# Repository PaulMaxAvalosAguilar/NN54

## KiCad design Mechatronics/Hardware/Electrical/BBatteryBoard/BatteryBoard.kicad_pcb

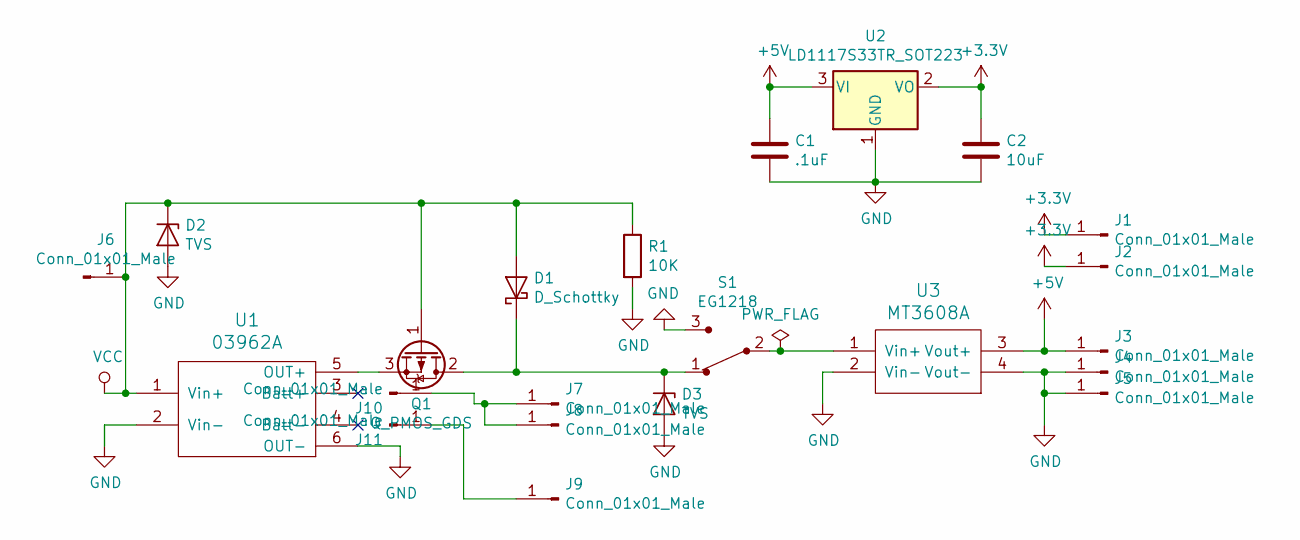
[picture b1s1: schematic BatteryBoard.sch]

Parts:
C1: .1uF; C_Disc_D9.0mm_W5.0mm_P5.00mm
C2: 10uF; C_Disc_D9.0mm_W5.0mm_P5.00mm
D1: D_Schottky; D_DO-201AD_P15.24mm_Horizontal
D2, D3: TVS; D_DO-201AD_P15.24mm_Horizontal
J1, J2, J3, J4, J5, J6, J7, J8, J9, J10, J11: Conn_01x01_Male; PinHeader_1x01_P2.54mm_Vertical
Q1: Q_PMOS_GDS; TO-220-3_Horizontal_TabDown
R1: 10K; R_Axial_DIN0414_L11.9mm_D4.5mm_P15.24mm_Horizontal
S1: EG1218; Switch_Slide_11.6x4mm_EG1218; MPN EG1218; Digi-Key_PN EG1903-ND
U1: 03962A
U2: LD1117S33TR_SOT223; TO-220-3_Horizontal_TabDown
U3: MT3608A; Mt3608

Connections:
+3V3: C2.1, J1.1, J2.1, U2.2 (VO)
+5V: C1.1, J3.1, U2.3 (VI), U3.3 (Vout+)
GND: C1.2, C2.2, D2.2 (A), D3.2 (A), J4.1, J5.1, R1.2, S1.3, U1.2 (Vin-), U1.6 (OUT-), U2.1 (GND), U3.2 (Vin-), U3.4 (Vout-)
unnamed: D1.1 (K), D3.1 (K), Q1.2 (D), S1.1
unnamed: J7.1, J8.1, J10.1
unnamed: J9.1, J11.1
unnamed: Q1.3 (S), U1.5 (OUT+)
unnamed: S1.2, U3.1 (Vin+)
VCC: D1.2 (A), D2.1 (K), J6.1, Q1.1 (G), R1.1, U1.1 (Vin+)

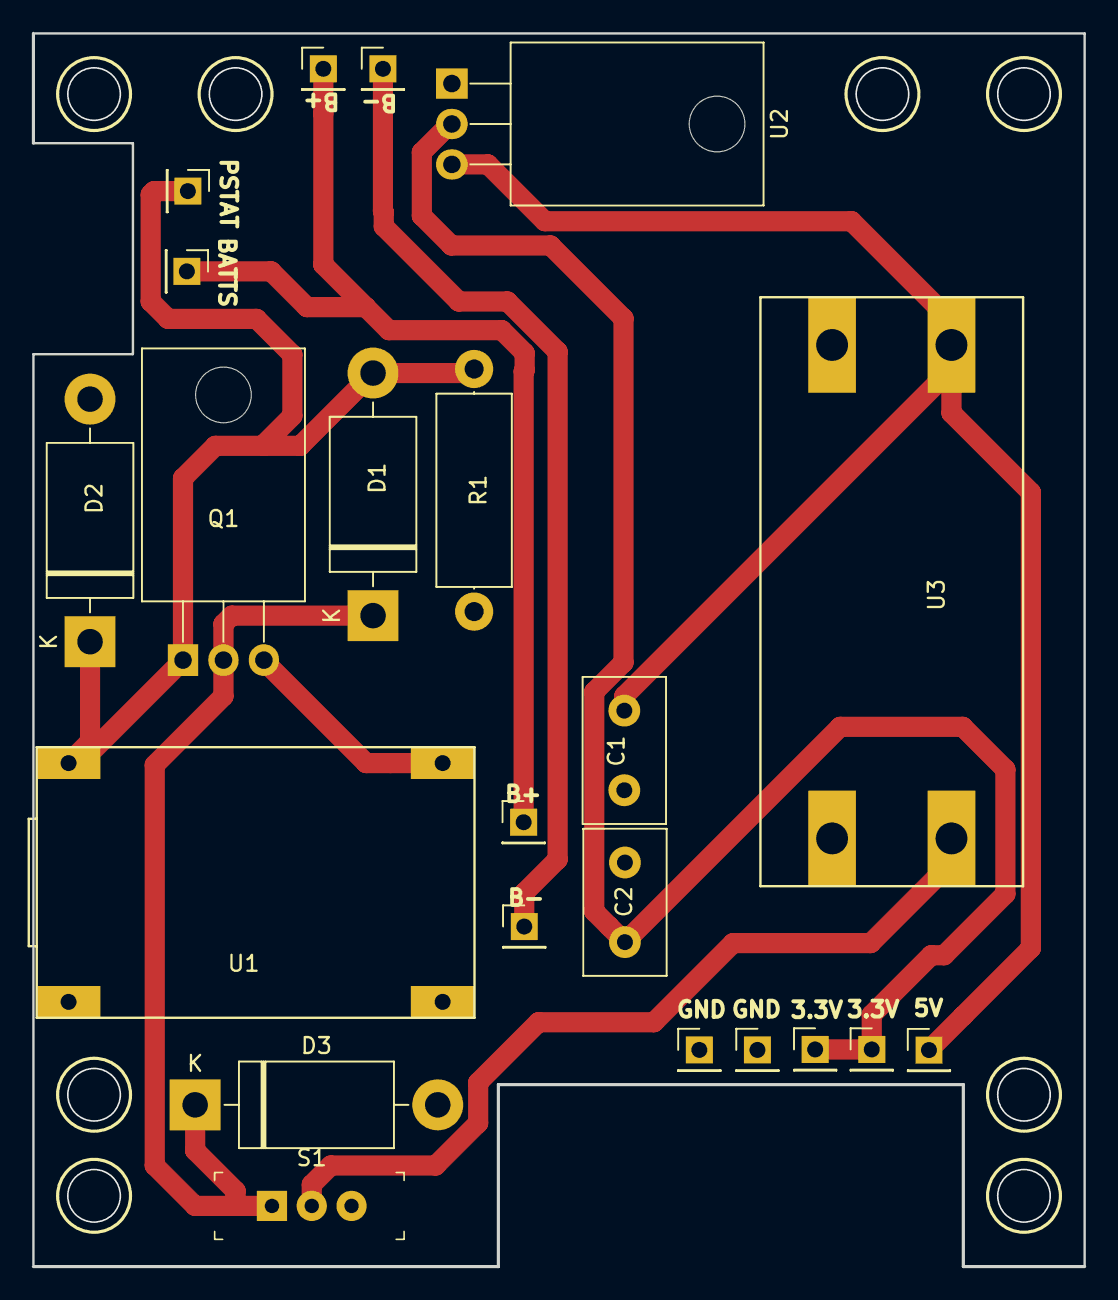
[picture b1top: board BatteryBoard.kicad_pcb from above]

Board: 2 copper layers, 66.0 x 77.5 mm, 22 parts (0 on the bottom side), 9 nets.

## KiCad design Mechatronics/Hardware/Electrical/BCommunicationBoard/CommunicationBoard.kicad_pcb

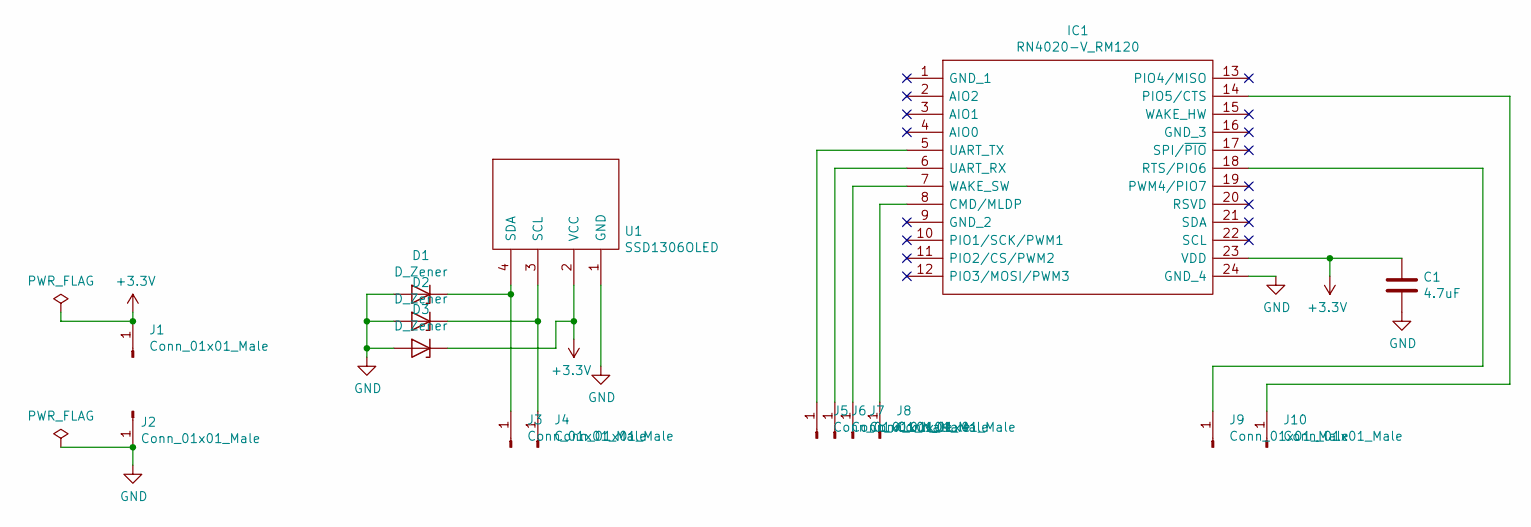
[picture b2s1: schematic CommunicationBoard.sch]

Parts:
C1: 4.7uF; C_Disc_D9.0mm_W5.0mm_P5.00mm
D1, D2, D3: D_Zener; D_DO-201AD_P15.24mm_Horizontal
IC1: RN4020-V_RM120; Bluetooth_Module_RN4020; Manufacturer_Part_Number RN4020-V/RM120
J1, J2, J3, J4, J5, J6, J7, J8, J9, J10: Conn_01x01_Male; PinHeader_1x01_P2.54mm_Vertical
U1: SSD1306OLED; SSD1306

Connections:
+3V3: C1.1, D3.1 (K), IC1.23 (VDD), J1.1, U1.2 (VCC)
GND: C1.2, D1.2 (A), D2.2 (A), D3.2 (A), IC1.24 (GND_4), J2.1, U1.1 (GND)
unnamed: D1.1 (K), J3.1, U1.4 (SDA)
unnamed: D2.1 (K), J4.1, U1.3 (SCL)
unnamed: IC1.5 (UART_TX), J5.1
unnamed: IC1.6 (UART_RX), J6.1
unnamed: IC1.7 (WAKE_SW), J7.1
unnamed: IC1.8 (CMD/MLDP), J8.1
unnamed: IC1.14 (PIO5/CTS), J10.1
unnamed: IC1.18 (RTS/PIO6), J9.1

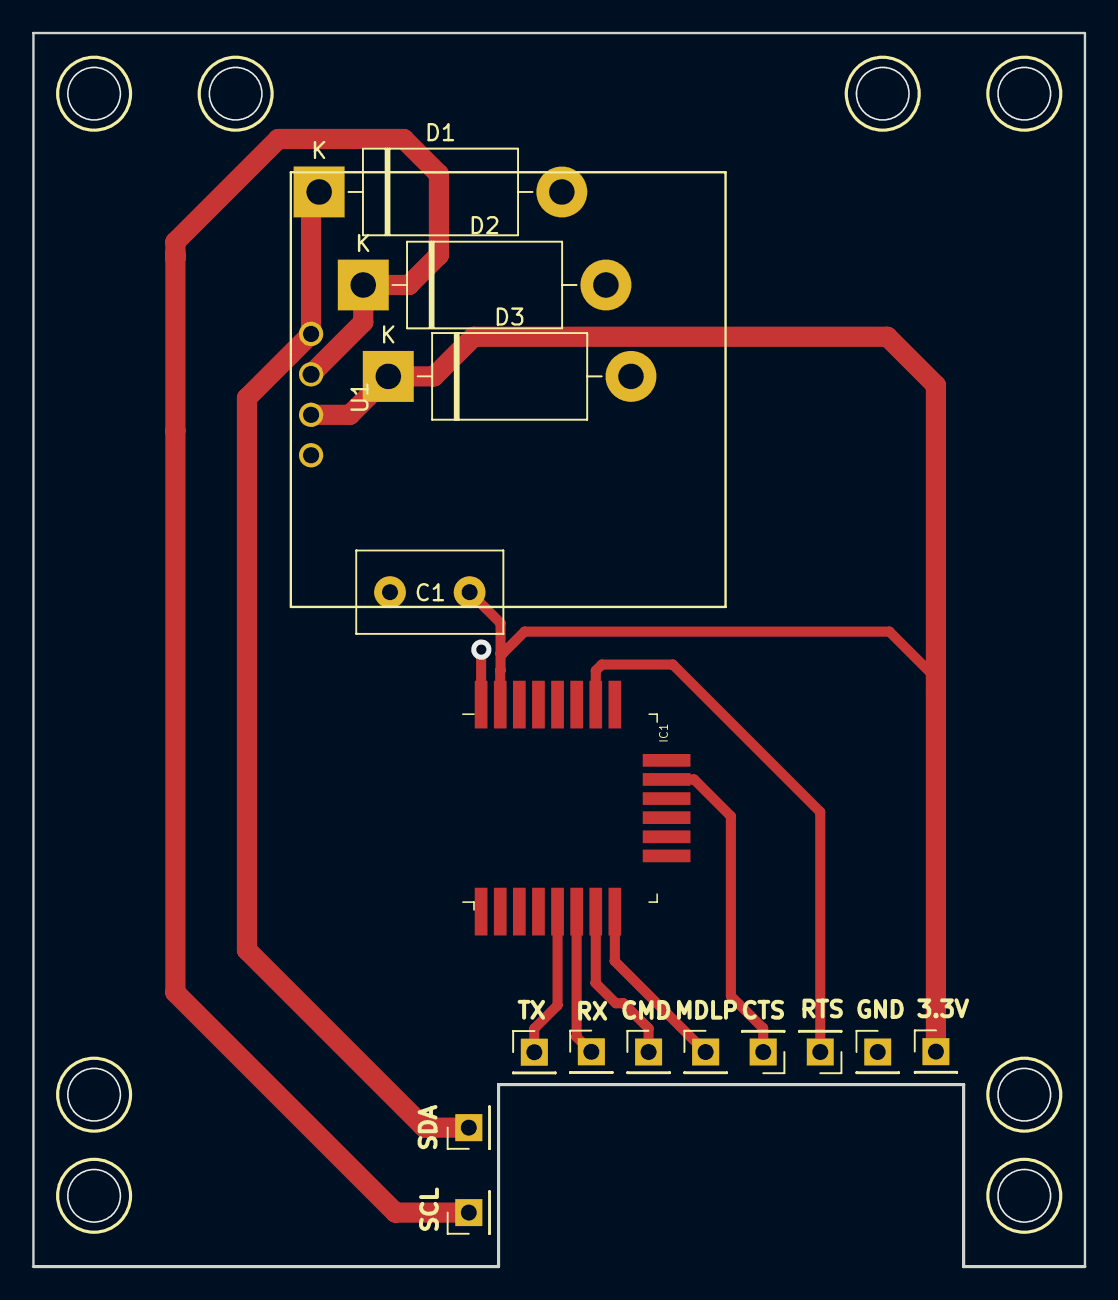
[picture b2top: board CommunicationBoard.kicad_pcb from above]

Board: 2 copper layers, 66.0 x 77.5 mm, 16 parts (0 on the bottom side), 10 nets.

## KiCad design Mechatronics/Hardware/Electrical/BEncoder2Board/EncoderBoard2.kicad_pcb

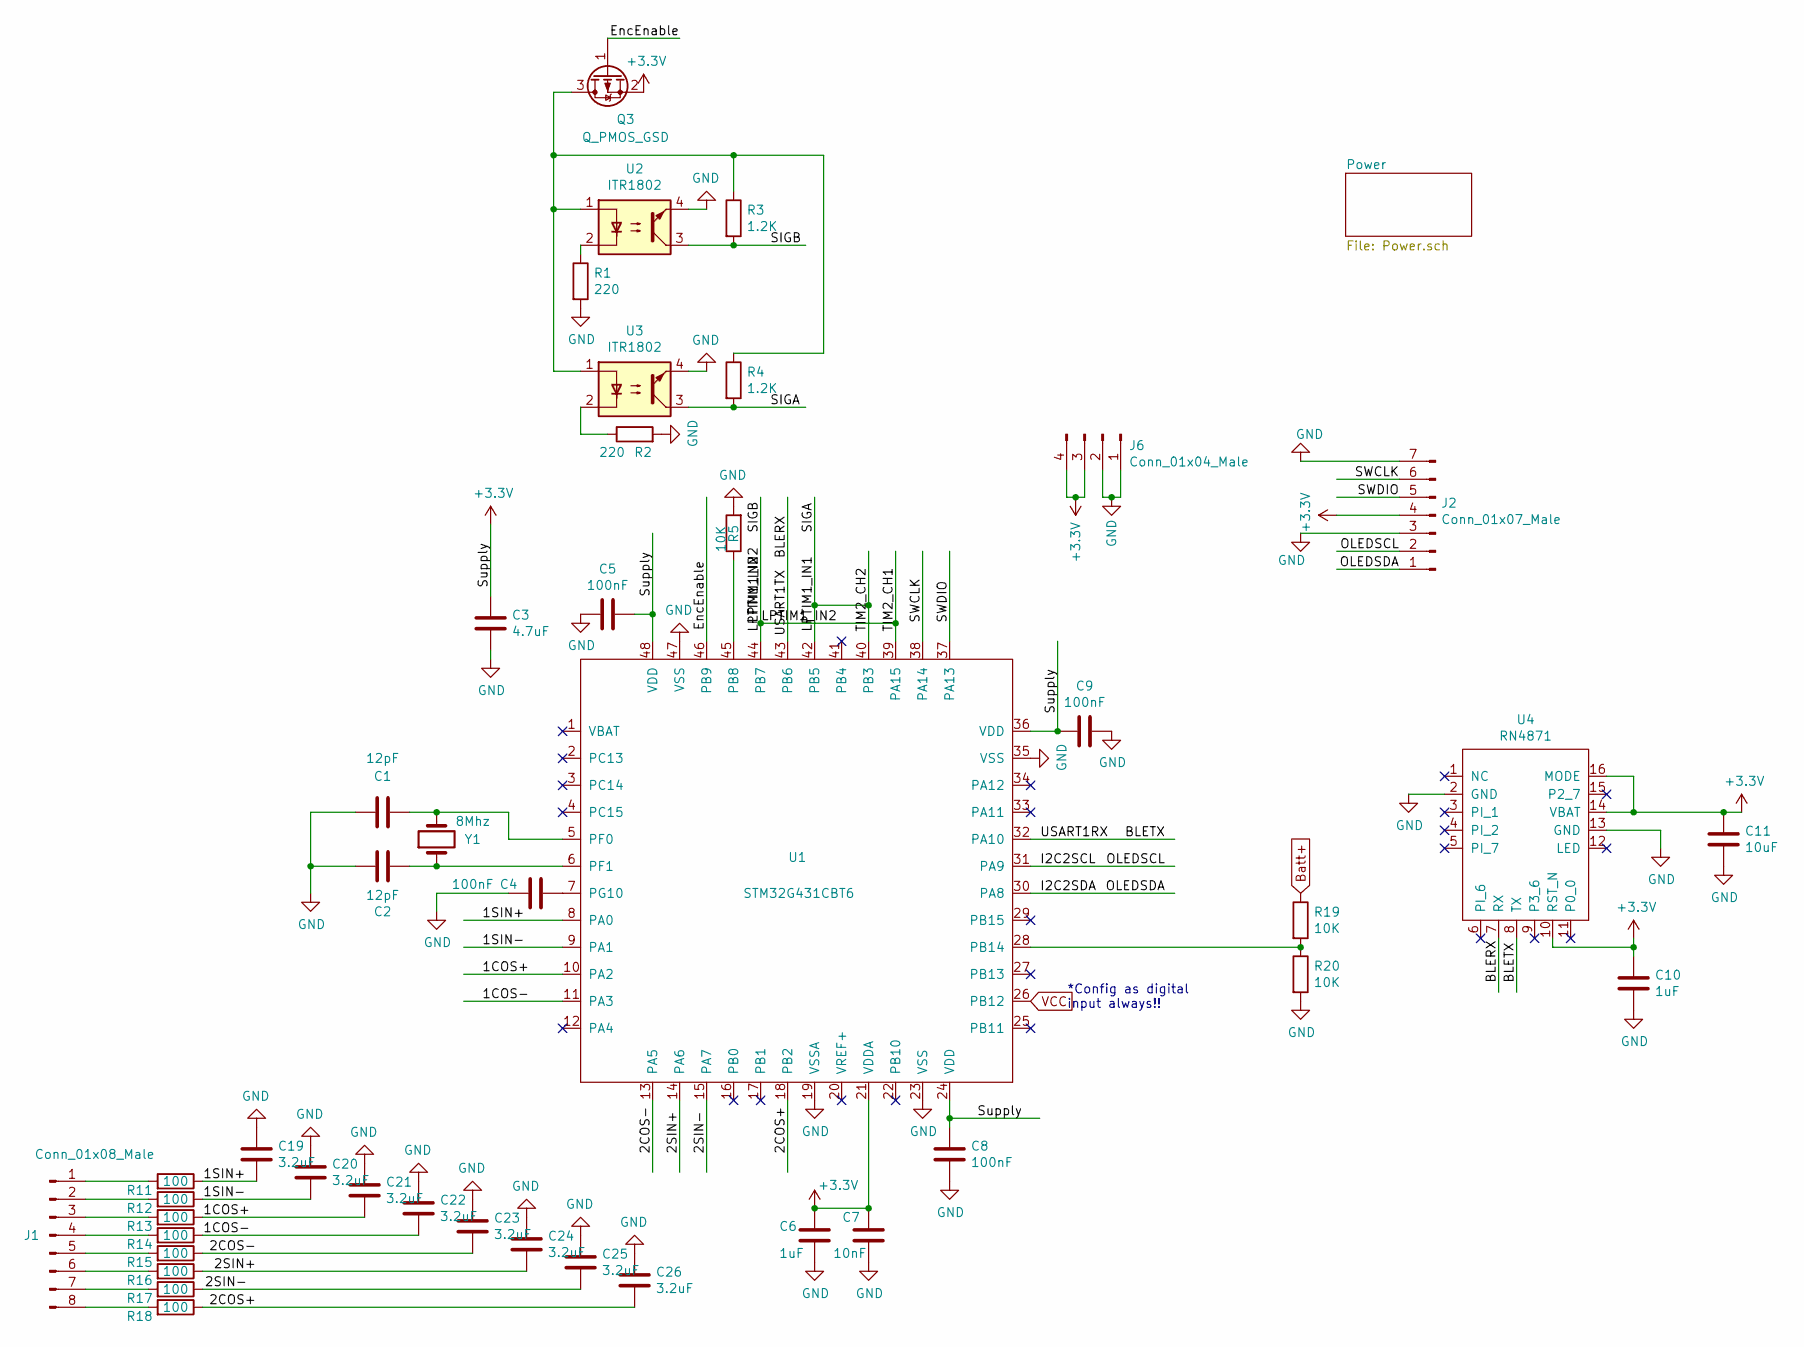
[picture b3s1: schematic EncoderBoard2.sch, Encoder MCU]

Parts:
C1, C2: 12pF; C_0603_1608Metric_Pad1.05x0.95mm_HandSolder
C3: 4.7uF; C_0603_1608Metric_Pad1.05x0.95mm_HandSolder
C4, C5, C8, C9: 100nF; C_0603_1608Metric_Pad1.05x0.95mm_HandSolder
C6, C10: 1uF; C_0603_1608Metric_Pad1.05x0.95mm_HandSolder
C7: 10nF; C_0603_1608Metric_Pad1.05x0.95mm_HandSolder
C11: 10uF; C_0603_1608Metric_Pad1.05x0.95mm_HandSolder
C19, C20, C21, C22, C23, C24, C25, C26: 3.2uF; C_0603_1608Metric_Pad1.05x0.95mm_HandSolder
J1: Conn_01x08_Male; PinHeader_1x08_P2.54mm_Vertical
J2: Conn_01x07_Male; PinHeader_1x07_P2.54mm_Vertical
J6: Conn_01x04_Male; PinHeader_2x02_P2.54mm_Vertical
Q3: Q_PMOS_GSD; SOT-23
R1, R2: 220; R_0603_1608Metric_Pad1.05x0.95mm_HandSolder
R3, R4: 1.2K; R_0603_1608Metric_Pad1.05x0.95mm_HandSolder
R5, R19, R20: 10K; R_0603_1608Metric_Pad1.05x0.95mm_HandSolder
R11, R12, R13, R14, R15, R16, R17, R18: 100; R_0603_1608Metric_Pad1.05x0.95mm_HandSolder
U1: STM32G431CBT6; LQFP-48_7x7mm_P0.5mm
U2, U3: ITR1802; OptointerrupterSmall
U4: RN4871; Bluetooth_Module_RN4871
Y1: 8Mhz; Crystal_HC49-U_Vertical

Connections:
+3V3: C3.1, C5.1, C6.1, C7.1, C8.1, C9.2, C10.1, C11.1, J2.4, J6.3, J6.4, Q3.2 (S), U1.21 (VDDA), U1.24 (VDD), U1.36 (VDD), U1.48 (VDD), U4.10 (RST_N), U4.14 (VBAT), U4.16 (MODE); also elsewhere on the board
/1COS+: C21.2, R13.1, U1.10 (PA2)
/1COS-: C22.2, R14.1, U1.11 (PA3)
/1SIN+: C19.2, R11.1, U1.8 (PA0)
/1SIN-: C20.2, R12.1, U1.9 (PA1)
/2COS+: C26.2, R18.1, U1.18 (PB2)
/2COS-: C23.2, R15.1, U1.13 (PA5)
/2SIN+: C24.2, R16.1, U1.14 (PA6)
/2SIN-: C25.2, R17.1, U1.15 (PA7)
/BLERX: U1.43 (PB6), U4.7 (RX)
/BLETX: U1.32 (PA10), U4.8 (TX)
/EncEnable: Q3.1 (G), U1.46 (PB9)
/I2C2SCL: J2.2, U1.31 (PA9)
/I2C2SDA: J2.1, U1.30 (PA8)
/LPTIM1_IN1: R4.2, U1.40 (PB3), U1.42 (PB5), U3.3
/LPTIM1_IN2: R3.2, U1.39 (PA15), U1.44 (PB7), U2.3
/SWCLK: J2.6, U1.38 (PA14)
/SWDIO: J2.5, U1.37 (PA13)
Batt+: R19.1; also elsewhere on the board
GND: C1.1, C2.1, C3.2, C4.2, C5.2, C6.2, C7.2, C8.2, C9.1, C10.2, C11.2, C19.1, C20.1, C21.1, C22.1, C23.1, C24.1, C25.1, C26.1, J2.3, J2.7, J6.1, J6.2, R1.2, R2.2, R5.2, R20.2, U1.19 (VSSA), U1.23 (VSS), U1.35 (VSS), U1.47 (VSS), U2.4, U3.4, U4.2 (GND), U4.13 (GND); also elsewhere on the board
unnamed: C1.2, U1.5 (PF0), Y1.2
unnamed: C2.2, U1.6 (PF1), Y1.1
unnamed: C4.1, U1.7 (PG10)
unnamed: J1.1, R11.2
unnamed: J1.2, R12.2
unnamed: J1.3, R13.2
unnamed: J1.4, R14.2
unnamed: J1.5, R15.2
unnamed: J1.6, R16.2
unnamed: J1.7, R17.2
unnamed: J1.8, R18.2
unnamed: Q3.3 (D), R3.1, R4.1, U2.1, U3.1
unnamed: R1.1, U2.2
unnamed: R2.1, U3.2
unnamed: R5.1, U1.45 (PB8)
unnamed: R19.2, R20.1, U1.28 (PB14)
VCC: U1.26 (PB12); also elsewhere on the board

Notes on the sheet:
*Config as digital input always!!

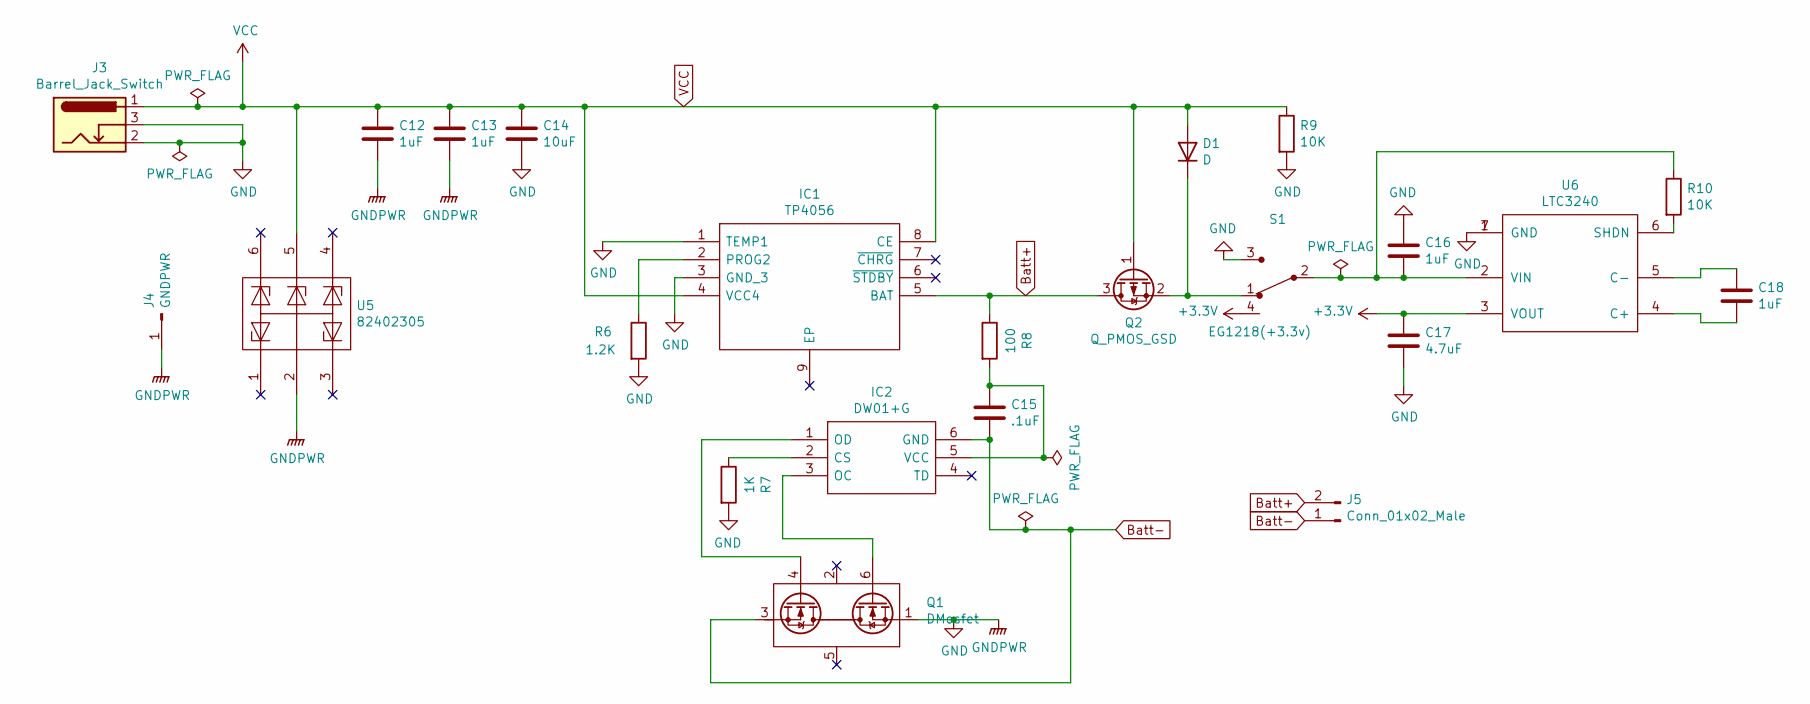
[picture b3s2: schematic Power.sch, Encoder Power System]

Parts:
C12, C13, C16, C18: 1uF; C_0603_1608Metric_Pad1.05x0.95mm_HandSolder
C14: 10uF; C_0603_1608Metric_Pad1.05x0.95mm_HandSolder
C15: .1uF; C_0603_1608Metric_Pad1.05x0.95mm_HandSolder
C17: 4.7uF; C_0603_1608Metric_Pad1.05x0.95mm_HandSolder
D1: D; D_SMA
IC1: TP4056; Sop(8); Manufacturer_Part_Number TP4056
IC2: DW01+G; Sot-23(6); Manufacturer_Part_Number DW01+G
J3: Barrel_Jack_Switch; BarrelJack_Horizontal
J4: GNDPWR; PinHeader_1x01_P2.54mm_Vertical
J5: Conn_01x02_Male; PinHeader_1x02_P2.54mm_Vertical
Q1: DMosfet; Sot-23(6)
Q2: Q_PMOS_GSD; SOT-23
R6: 1.2K; R_0603_1608Metric_Pad1.05x0.95mm_HandSolder
R7: 1K; R_0603_1608Metric_Pad1.05x0.95mm_HandSolder
R8: 100; R_0603_1608Metric_Pad1.05x0.95mm_HandSolder
R9, R10: 10K; R_0603_1608Metric_Pad1.05x0.95mm_HandSolder
S1: EG1218(+3.3v); PinHeader_1x04_P2.54mm_Vertical; MPN EG1218; Digi-Key_PN EG1903-ND
U5: 82402305; Sot-23(6)
U6: LTC3240; DFN-6_DC

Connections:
+3V3: C17.1, S1.4, U6.3 (VOUT); also elsewhere on the board
Batt+: IC1.5 (BAT), J5.2, Q2.3 (D), R8.1; also elsewhere on the board
Batt-: C15.2, IC2.6 (GND), J5.1, Q1.3 (S)
GND: C12.2, C13.2, C14.2, C16.1, C17.2, IC1.1 (TEMP1), IC1.3 (GND_3), J3.2, J3.3, J4.1, Q1.1 (S), R6.2, R7.2, R9.2, S1.3, U5.2, U6.1 (GND), U6.7 (GND); also elsewhere on the board
unnamed: C15.1, IC2.5 (VCC), R8.2
unnamed: C16.2, R10.1, S1.2, U6.2 (VIN)
unnamed: C18.1, U6.5 (C-)
unnamed: C18.2, U6.4 (C+)
unnamed: D1.1 (K), Q2.2 (S), S1.1
unnamed: IC1.2 (PROG2), R6.1
unnamed: IC2.1 (OD), Q1.4 (G)
unnamed: IC2.2 (CS), R7.1
unnamed: IC2.3 (OC), Q1.6 (G)
unnamed: R10.2, U6.6 (SHDN)
VCC: C12.1, C13.1, C14.1, D1.2 (A), IC1.4 (VCC4), IC1.8 (CE), J3.1, Q2.1 (G), R9.1, U5.5; also elsewhere on the board

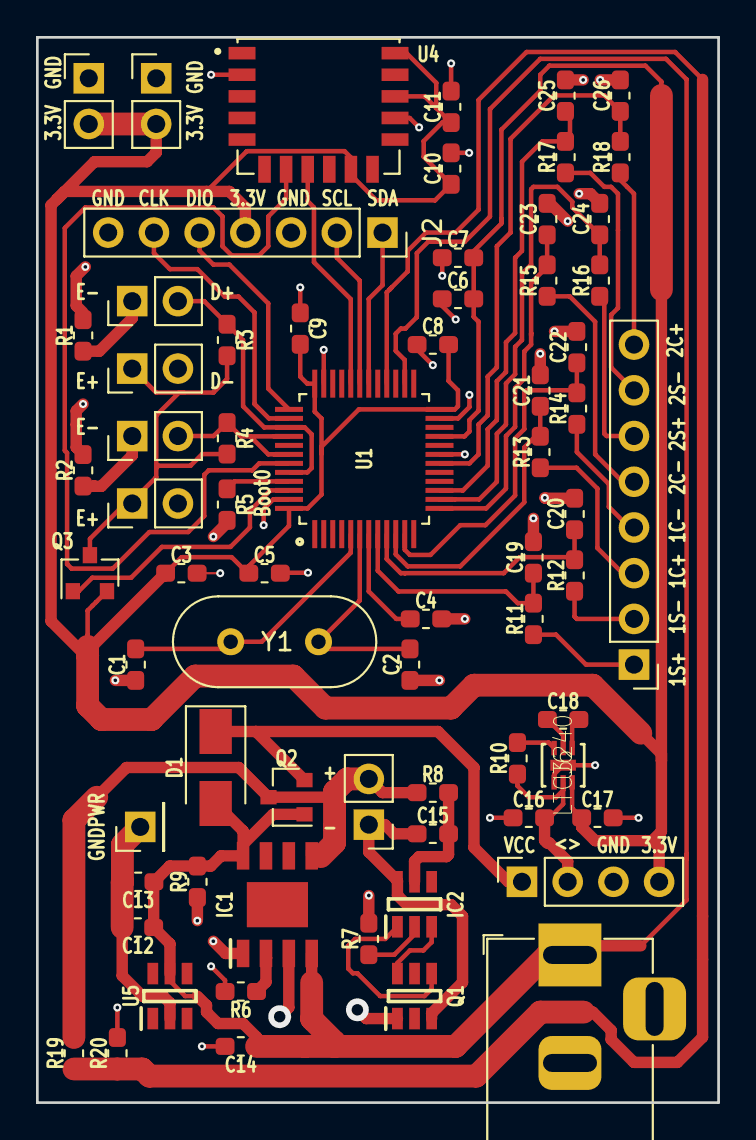
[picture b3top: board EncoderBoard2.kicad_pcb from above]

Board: 2 copper layers, 37.8 x 59.2 mm, 66 parts (0 on the bottom side), 48 nets.

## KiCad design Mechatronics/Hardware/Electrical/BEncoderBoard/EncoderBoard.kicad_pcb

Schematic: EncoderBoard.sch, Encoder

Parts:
C1, C2, C3, C5, C9, C10: 100nF; C_0603_1608Metric_Pad1.05x0.95mm_HandSolder
C4, C11, C14, C17, C18: 1uF; C_0603_1608Metric_Pad1.05x0.95mm_HandSolder
C6, C13: 10uF; C_0603_1608Metric_Pad1.05x0.95mm_HandSolder
C7, C8: 12pF; C_0603_1608Metric_Pad1.05x0.95mm_HandSolder
C12, C15: 4.7uF; C_0603_1608Metric_Pad1.05x0.95mm_HandSolder
C16: .1uF; C_0603_1608Metric_Pad1.05x0.95mm_HandSolder
D1: D; D_SMA
IC1: RN4020-V_RM120; Bluetooth_Module_RN4020; Manufacturer_Part_Number RN4020-V/RM120
IC2: TP4056; Sop(8); Manufacturer_Part_Number TP4056
IC3: DW01+G; Sot-23(6); Manufacturer_Part_Number DW01+G
J1: Conn_01x07_Male; PinSocket_1x07_P2.54mm_Vertical
J2: GNDPWR; No3dmodelPinHeader_1x01_P2.54mm_Vertical
J4: Barrel_Jack_Switch; BarrelJack_Horizontal
J5: Batt+; No3dmodelPinHeader_1x01_P2.54mm_Vertical
J7: Batt-; No3dmodelPinHeader_1x01_P2.54mm_Vertical
Q1: DMosfet; Sot-23(6)
Q2, Q3: Q_PMOS_GSD; SOT-23
R1, R2: 220; R_0603_1608Metric_Pad1.05x0.95mm_HandSolder
R3, R4, R8: 1.2K; R_0603_1608Metric_Pad1.05x0.95mm_HandSolder
R5, R6, R7, R10, R12, R13, R14, R15, R16: 10K; R_0603_1608Metric_Pad1.05x0.95mm_HandSolder
R9: 1K; R_0603_1608Metric_Pad1.05x0.95mm_HandSolder
R11: 100; R_0603_1608Metric_Pad1.05x0.95mm_HandSolder
S1: EG1218; Switch_Slide_11.6x4mm_EG1218; MPN EG1218; Digi-Key_PN EG1903-ND
U1: STM32F103C8T6; QFP50P900X900X160-48N
U2, U3: ITR1802; OptointerrupterConnector
U4: 82402305; Sot-23(6)
U5: SSD1306OLED; PinSocket_1x04_P2.54mm_Vertical
U6: LTC3240; DFN-6_DC
Y1: 8Mhz; Crystal_HC49-U_Vertical

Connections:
+3V3: C1.1, C3.2, C4.2, C5.1, C6.2, C9.1, C10.1, C12.1, C15.1, IC1.23 (VDD), Q3.2 (S), R10.1, R12.1, U1.1 (VBAT), U1.9 (VDDA), U1.24 (VDD), U1.36 (VDD), U1.48 (VDD), U5.2 (VCC), U6.3 (VOUT)
/BOOT0: R5.1, U1.44 (BOOT0)
/Batt+: IC2.5, J5.1, Q2.3 (D), R11.1, R13.1
/CTS: IC1.14 (PIO5/CTS), J1.3
/EncEnable: Q3.1 (G), U1.14 (PA4)
/F1RX: IC1.5 (UART_TX), J1.5, R12.2, U1.43 (*PB7)
/F1SCL: U1.45 (*PB8), U5.3 (SCL)
/F1SDA: U1.46 (*PB9), U5.4 (SDA)
/F1TX: IC1.6 (UART_RX), J1.4, R10.2, U1.42 (*PB6)
/RTS: IC1.18 (RTS/PIO6), J1.6
/SIGA: R4.2, U1.31 (*PA10), U1.38 (*PA15), U3.3
/SIGB: R3.2, U1.29 (*PA8), U1.39 (*PB3), U2.3
/SWCLK: J1.2, U1.37 (*PA14/SWCLK)
/SWDIO: J1.1, U1.34 (*PA13/SWDIO)
GND: C1.2, C2.2, C3.1, C4.1, C5.2, C6.1, C7.1, C8.1, C9.2, C10.2, C11.1, C12.2, C13.2, C15.2, C16.2, C17.2, C18.2, IC1.1 (GND_1), IC1.24 (GND_4), IC2.1, IC2.3, IC3.6, J1.7, J2.1, J4.2, J4.3, J7.1, Q1.1 (S), Q1.3 (S), R1.2, R2.2, R5.2, R6.2, R8.2, R9.2, R14.2, R16.2, S1.3, U1.8 (VSSA), U1.20 (BOOT1/*PB2), U1.23 (VSS), U1.35 (VSS), U1.47 (VSS), U2.4, U3.4, U4.2, U5.1 (GND), U6.1 (GND), U6.7 (GND)
unnamed: C2.1, U1.7 (NRST)
unnamed: C7.2, U1.5 (PD0_OSC_IN), Y1.1
unnamed: C8.2, U1.6 (PD1_OSC_OUT), Y1.2
unnamed: C11.2, R7.1, S1.2, U6.2 (VIN)
unnamed: C14.1, U6.5 (C-)
unnamed: C14.2, U6.4 (C+)
unnamed: C16.1, IC3.5, R11.2
unnamed: D1.1 (K), Q2.2 (S), S1.1
unnamed: IC1.7 (WAKE_SW), U1.41 (PB5)
unnamed: IC2.2, R8.1
unnamed: IC3.1, Q1.4 (G)
unnamed: IC3.2, R9.1
unnamed: IC3.3, Q1.6 (G)
unnamed: Q3.3 (D), R3.1, R4.1, U2.1, U3.1
unnamed: R1.1, U2.2
unnamed: R2.1, U3.2
unnamed: R7.2, U6.6 (SHDN)
unnamed: R13.2, R14.1, U1.11 (PA1)
unnamed: R15.2, R16.1, U1.25 (*PB12)
VCC: C13.1, C17.1, C18.1, D1.2 (A), IC2.4, IC2.8, J4.1, Q2.1 (G), R6.1, R15.1, U4.5

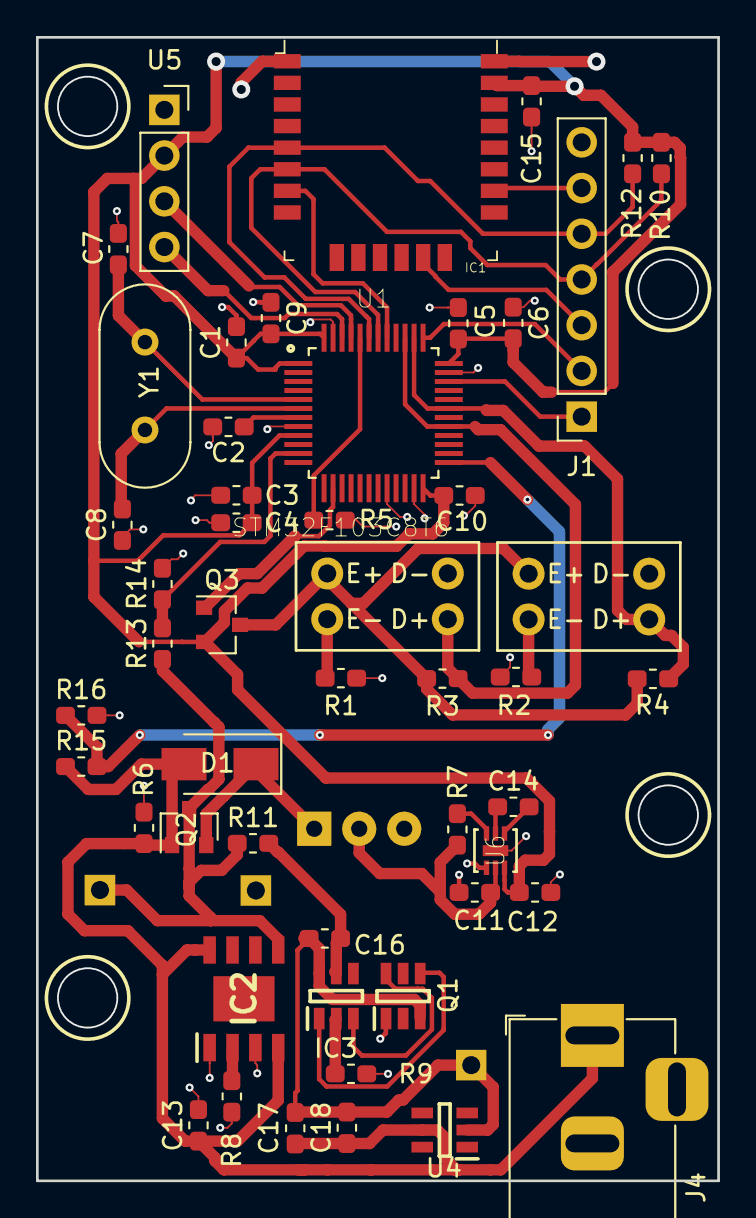
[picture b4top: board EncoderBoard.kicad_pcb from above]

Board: 2 copper layers, 37.8 x 63.5 mm, 54 parts (0 on the bottom side), 35 nets.

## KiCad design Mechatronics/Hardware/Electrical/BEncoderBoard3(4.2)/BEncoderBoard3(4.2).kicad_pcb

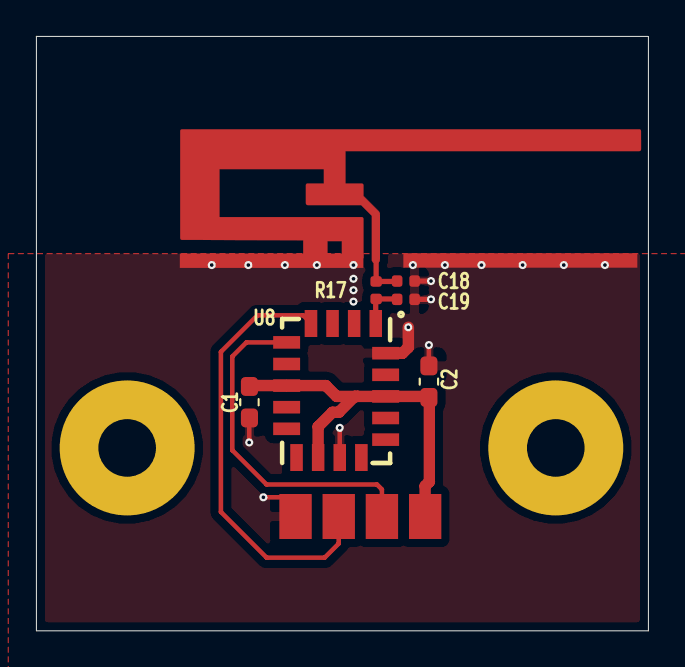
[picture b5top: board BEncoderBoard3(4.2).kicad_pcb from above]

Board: 2 copper layers, 34.0 x 33.0 mm, 8 parts (0 on the bottom side), 6 nets.

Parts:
AE1: LOGO; Antenna
C1: 1uF; C_0603_1608Metric_Pad1.05x0.95mm_HandSolder
C2: 10uF; C_0603_1608Metric_Pad1.05x0.95mm_HandSolder
C18, C19: C_Rf; C_0402_1005Metric
J1: Conn_01x04_Male; SolderWirePad_1x04_SMD_5x10mm_copy
R17: L_Rf; L_0402_1005Metric
U8: RN4871U

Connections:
+3V3: C1.1, C2.1, J1.4, U8.7, U8.11, U8.16
GND: AE1.2, C1.2, C2.2, C18.2, C19.2, J1.1, U8.12, U8.18
unnamed: C18.1, R17.2
unnamed: C19.1, R17.1, U8.1
unnamed: J1.2, U8.4
unnamed: J1.3, U8.5

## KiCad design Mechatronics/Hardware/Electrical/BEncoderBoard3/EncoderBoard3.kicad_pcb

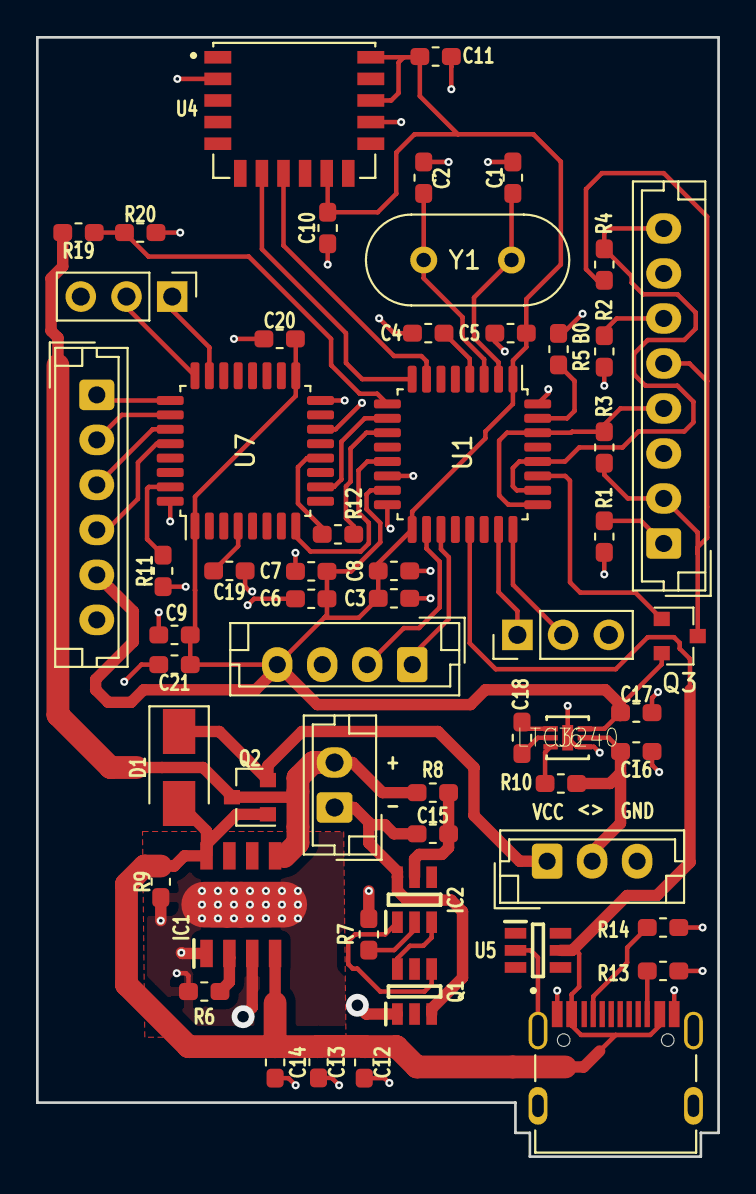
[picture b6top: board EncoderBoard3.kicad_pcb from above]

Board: 2 copper layers, 37.8 x 62.2 mm, 57 parts (0 on the bottom side), 46 nets.

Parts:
C1, C2: 12pF; C_0603_1608Metric_Pad1.05x0.95mm_HandSolder
C3, C17, C21: 4.7uF; C_0603_1608Metric_Pad1.05x0.95mm_HandSolder
C4, C5, C8, C9, C15, C19, C20: 100nF; C_0603_1608Metric_Pad1.05x0.95mm_HandSolder
C6, C10, C12, C13, C16, C18: 1uF; C_0603_1608Metric_Pad1.05x0.95mm_HandSolder
C7: 10nF; C_0603_1608Metric_Pad1.05x0.95mm_HandSolder
C11, C14: 10uF; C_0603_1608Metric_Pad1.05x0.95mm_HandSolder
D1: D; D_SMA
IC1: TP4056; Sop(8)
IC2: DW01+G; Sot-23(6)
J1: Sens_SWD; PinHeader_1x03_P2.54mm_Vertical
J2: SWD; PinHeader_1x03_P2.54mm_Vertical
J3: TYPE-C-31-M-12; HRO_TYPE-C-31-M-12
J5: Batt_Conn; JST_EH_B2B-EH-A_1x02_P2.50mm_Vertical
J6: Sens_SPI; JST_EH_B6B-EH-A_1x06_P2.50mm_Vertical
J7: I2C; JST_EH_B4B-EH-A_1x04_P2.50mm_Vertical
J8: Opto Sensors; JST_EH_B8B-EH-A_1x08_P2.50mm_Vertical
Q1: DMosfet; Sot-23(6)
Q2, Q3: Q_PMOS_GSD; SOT-23
R1, R2: 560; R_0603_1608Metric_Pad1.05x0.95mm_HandSolder
R3, R4: 1.2K; R_0603_1608Metric_Pad1.05x0.95mm_HandSolder
R5, R9, R10, R11, R19, R20: 10K; R_0603_1608Metric_Pad1.05x0.95mm_HandSolder
R6: 1.5K; R_0603_1608Metric_Pad1.05x0.95mm_HandSolder
R7, R12: 1K; R_0603_1608Metric_Pad1.05x0.95mm_HandSolder
R8: 100; R_0603_1608Metric_Pad1.05x0.95mm_HandSolder
R13: 5.1K; R_0603_1608Metric_Pad1.05x0.95mm_HandSolder
R14: 5.1k; R_0603_1608Metric_Pad1.05x0.95mm_HandSolder
S1: EG1218_Conn; JST_EH_B3B-EH-A_1x03_P2.50mm_Vertical
U1, U7: STM32G431KBT6; LQFP-32_7x7mm_P0.8mm
U4: RN4871; Bluetooth_Module_RN4871
U5: 82402305; Sot-23(6)
U6: LTC3240; DFN-6_DC
Y1: 8Mhz; Crystal_HC49-U_Vertical

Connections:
+3V3: C3.1, C5.1, C6.1, C7.1, C8.1, C9.1, C10.1, C11.1, C17.1, C20.1, C21.1, J6.5, J7.4, Q3.2, U1.1, U1.15, U1.17, U4.10, U4.14, U4.16, U6.3, U7.1, U7.17
/BLERX: U1.8, U4.7
/BLETX: U1.7, U4.8
/D+(a): J8.8, R4.2, U1.26, U1.28
/D+(b): J8.4, R3.2, U1.25, U1.30
/Data: U1.13, U7.8
/E+(a): J8.2, J8.5, Q3.3, R3.1, R4.1
/E-(a): J8.6, R2.1
/E-(b): J8.1, R1.1
/EncEnable: Q3.1, U1.27
/I2C2SCL: J7.1, U1.19
/I2C2SDA: J7.2, U1.18
/SPI1MISO: R12.2, U1.11
/SPI1SCK: U1.10, U7.10
/SWCLK: J2.2, U1.24
/SWDIO: J2.1, U1.23
/Sens_SPI1MOSI: R12.1, U7.12
/Sens_SPI3MISO: J6.3, U7.27
/Sens_SPI3MOSI: J6.4, U7.28
/Sens_SPI3NSS: J6.1, U7.25
/Sens_SPI3SCK: J6.2, U7.26
/Sens_SWCLK: J1.2, U7.24
/Sens_SWDIO: J1.1, U7.23
Batt+: IC1.5, J5.2, Q2.3, R8.1, R19.1
Batt-: C15.2, IC2.6, J5.1, Q1.3
GND: C1.1, C2.1, C3.2, C4.2, C5.2, C6.2, C7.2, C8.2, C9.2, C10.2, C11.2, C12.2, C13.2, C14.2, C16.1, C17.2, C19.2, C20.2, C21.2, IC1.1, IC1.3, IC1.9, J1.3, J2.3, J3.A1B12, J3.B1A12, J3.S1, J3.S2, J3.S3, J3.S4, J6.6, J7.3, J8.3, J8.7, Q1.1, R1.2, R2.2, R5.2, R6.2, R7.2, R9.2, R11.2, R13.2, R14.2, R20.2, S1.3, U1.14, U1.16, U1.32, U4.2, U4.13, U5.2, U6.1, U6.7, U7.14, U7.16, U7.32
unnamed: C1.2, U1.2, Y1.2
unnamed: C2.2, U1.3, Y1.1
unnamed: C4.1, U1.4
unnamed: C15.1, IC2.5, R8.2
unnamed: C16.2, R10.1, S1.2, U6.2
unnamed: C18.1, U6.5
unnamed: C18.2, U6.4
unnamed: C19.1, U7.4
unnamed: D1.1, Q2.2, S1.1
unnamed: IC1.2, R6.1
unnamed: IC2.1, Q1.4
unnamed: IC2.2, R7.1
unnamed: IC2.3, Q1.6
unnamed: J3.A5, R14.1
unnamed: J3.B5, R13.1
unnamed: R5.1, U1.31
unnamed: R10.2, U6.6
unnamed: R11.1, U7.31
unnamed: R19.2, R20.1, U1.9
VCC: C12.1, C13.1, C14.1, D1.2, IC1.4, IC1.8, J3.A4B9, J3.B4A9, Q2.1, R9.1, U1.21, U5.5

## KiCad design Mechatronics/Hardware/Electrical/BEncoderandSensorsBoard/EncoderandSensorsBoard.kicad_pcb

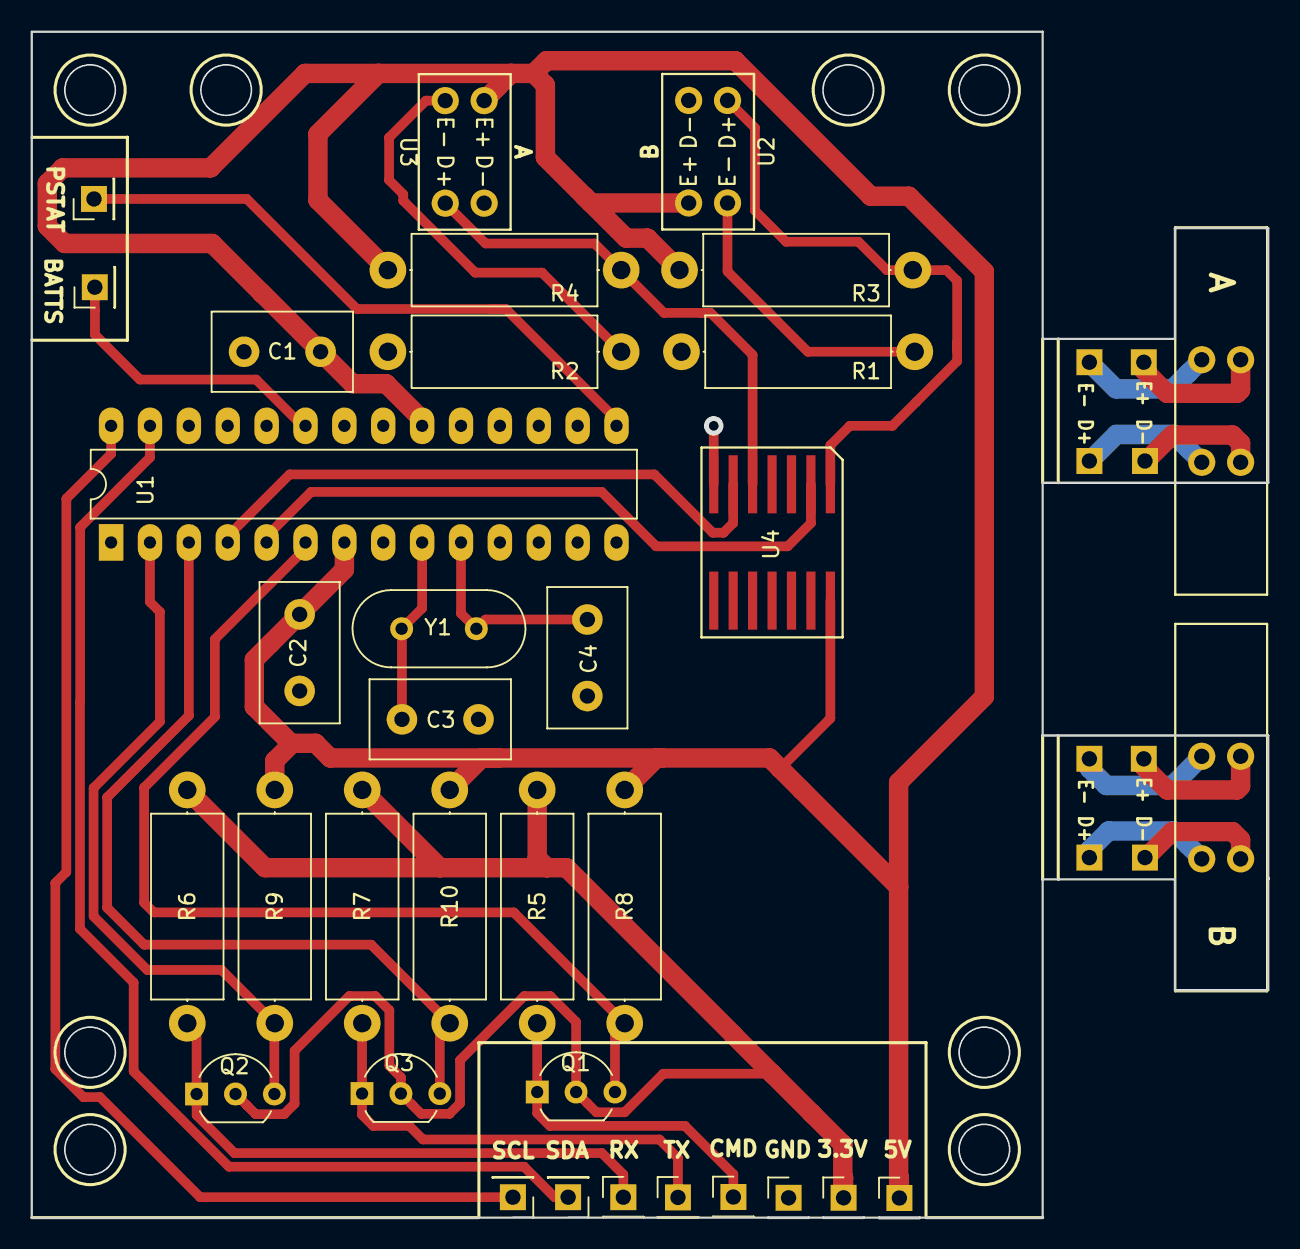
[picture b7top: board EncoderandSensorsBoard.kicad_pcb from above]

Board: 2 copper layers, 80.8 x 77.5 mm, 42 parts (0 on the bottom side), 29 nets.

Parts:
C1, C2: .1uF; C_Disc_D9.0mm_W5.0mm_P5.00mm
C3, C4: 22pF; C_Disc_D9.0mm_W5.0mm_P5.00mm
J1, J2, J3, J4, J5, J6, J7, J8, J9, J10: Conn_01x01_Male; PinHeader_1x01_P2.54mm_Vertical
J1#2, J2#2, J3#2, J4#2, J5#2, J6#2, J7#2, J8#2: Conn_01x01_Male; No3dmodelPinHeader_1x01_P2.54mm_Vertical
Q1, Q2, Q3: Q_NMOS_SGD; TO-92_Inline_Wide
R1, R2: 220; R_Axial_DIN0414_L11.9mm_D4.5mm_P15.24mm_Horizontal
R3, R4: 1.2K; R_Axial_DIN0414_L11.9mm_D4.5mm_P15.24mm_Horizontal
R5, R6, R7, R8, R9, R10: 10K; R_Axial_DIN0414_L11.9mm_D4.5mm_P15.24mm_Horizontal
U1: ATmega328-PU; DIP-28_W7.62mm_LongPads
U1#2, U2#2: ITR1802; itr8102
U2: ITR1802A; OptointerrupterConnector
U3: ITR1802B; OptointerrupterConnector
U4: HEF40106BT; SOIC-14
Y1: 20Mhz; Crystal_HC49-U_Vertical

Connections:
+3V3: J6.1, Q1.2, Q2.2, Q3.2, R5.1, R6.1, R7.1
+5V: C1.2, C2.1, J1.1, R3.1, R4.1, R8.1, R9.1, R10.1, U1.7, U1.20, U2.1, U3.1, U4.14
/3VCMD: J3.1, Q1.1, R5.2
/3VRX: J5.1, Q3.1, R7.2
/3VTX: J4.1, Q2.1, R6.2
/BattVoltSens: J10.1, U1.23
/CMD: Q1.3, R8.2, U1.6
/OUTA: U1.4, U4.6
/OUTB: U1.5, U4.2
/PowSupStat: J9.1, U1.15
/RX: Q2.3, R9.2, U1.2
/SCL: J8.1, U1.28
/SDA: J7.1, U1.27
/SIGA: R4.2, U3.3, U4.5
/SIGB: R3.2, U2.3, U4.1
/TX: Q3.3, R10.2, U1.3
GND: C1.1, C2.2, C3.1, C4.1, J2.1, R1.2, R2.2, U1.8, U1.22, U2.4, U3.4, U4.7
unnamed: C3.2, U1.9, Y1.1
unnamed: C4.2, U1.10, Y1.2
unnamed: J1#2.1, U1#2.1
unnamed: J2#2.1, U1#2.2
unnamed: J3#2.1, U1#2.4
unnamed: J4#2.1, U1#2.3
unnamed: J5#2.1, U2#2.1
unnamed: J6#2.1, U2#2.2
unnamed: J7#2.1, U2#2.4
unnamed: J8#2.1, U2#2.3
unnamed: R1.1, U2.2
unnamed: R2.1, U3.2

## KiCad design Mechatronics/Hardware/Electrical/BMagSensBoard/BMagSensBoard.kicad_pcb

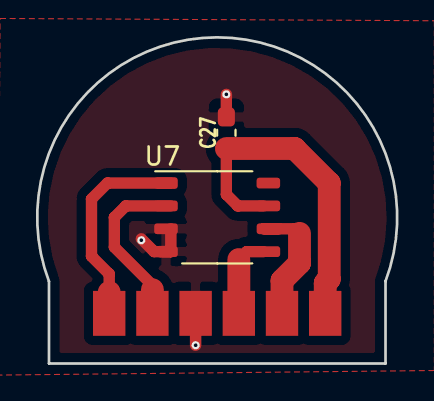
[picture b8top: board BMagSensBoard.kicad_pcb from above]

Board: 2 copper layers, 20.0 x 18.1 mm, 3 parts (0 on the bottom side), 6 nets.

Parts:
C27: 100nF; C_0603_1608Metric_Pad1.05x0.95mm_HandSolder
J7: Conn_01x06_Male; SolderWirePad_1x01_SMD_5x10mm
U7: TLE5009; SO-8_3.9x4.9mm_P1.27mm

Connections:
/COS_N: J7.2, U7.2
/COS_P: J7.1, U7.1
/SIN_N: J7.5, U7.6
/SIN_P: J7.4, U7.5
/VDD: C27.1, J7.6, U7.7
GND: C27.2, J7.3, U7.3, U7.4
